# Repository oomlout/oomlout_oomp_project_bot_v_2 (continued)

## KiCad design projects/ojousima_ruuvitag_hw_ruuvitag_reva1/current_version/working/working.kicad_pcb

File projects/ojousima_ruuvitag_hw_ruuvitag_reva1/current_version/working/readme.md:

# ruuvitag_hw
 
## summary 
* id: ojousima_ruuvitag_hw_ruuvitag_reva1
* user: ojousima
* name: ruuvitag_hw
* board: ruuvitag_reva1
* repo: https://github.com/ojousima/ruuvitag_hw
* src_file_repo_kicad_pcb: ruuvitag_reva1/ruuvitag_reva1.kicad_pcb
* src_file_repo_kicad_pcb_link: https://github.com/ojousima/ruuvitag_hw/tree/master/ruuvitag_reva1/ruuvitag_reva1.kicad_pcb

* src_file_repo_sch: ruuvitag_reva1/ruuvitag_reva1.sch
* src_file_repo_sch_link: https://github.com/ojousima/ruuvitag_hw/tree/master/ruuvitag_reva1/ruuvitag_reva1.sch
* full details link: https://github.com/oomlout/oomlout_oomp_project_bot_v_2/tree/main/projects/ojousima_ruuvitag_hw_ruuvitag_reva1/current_version/working

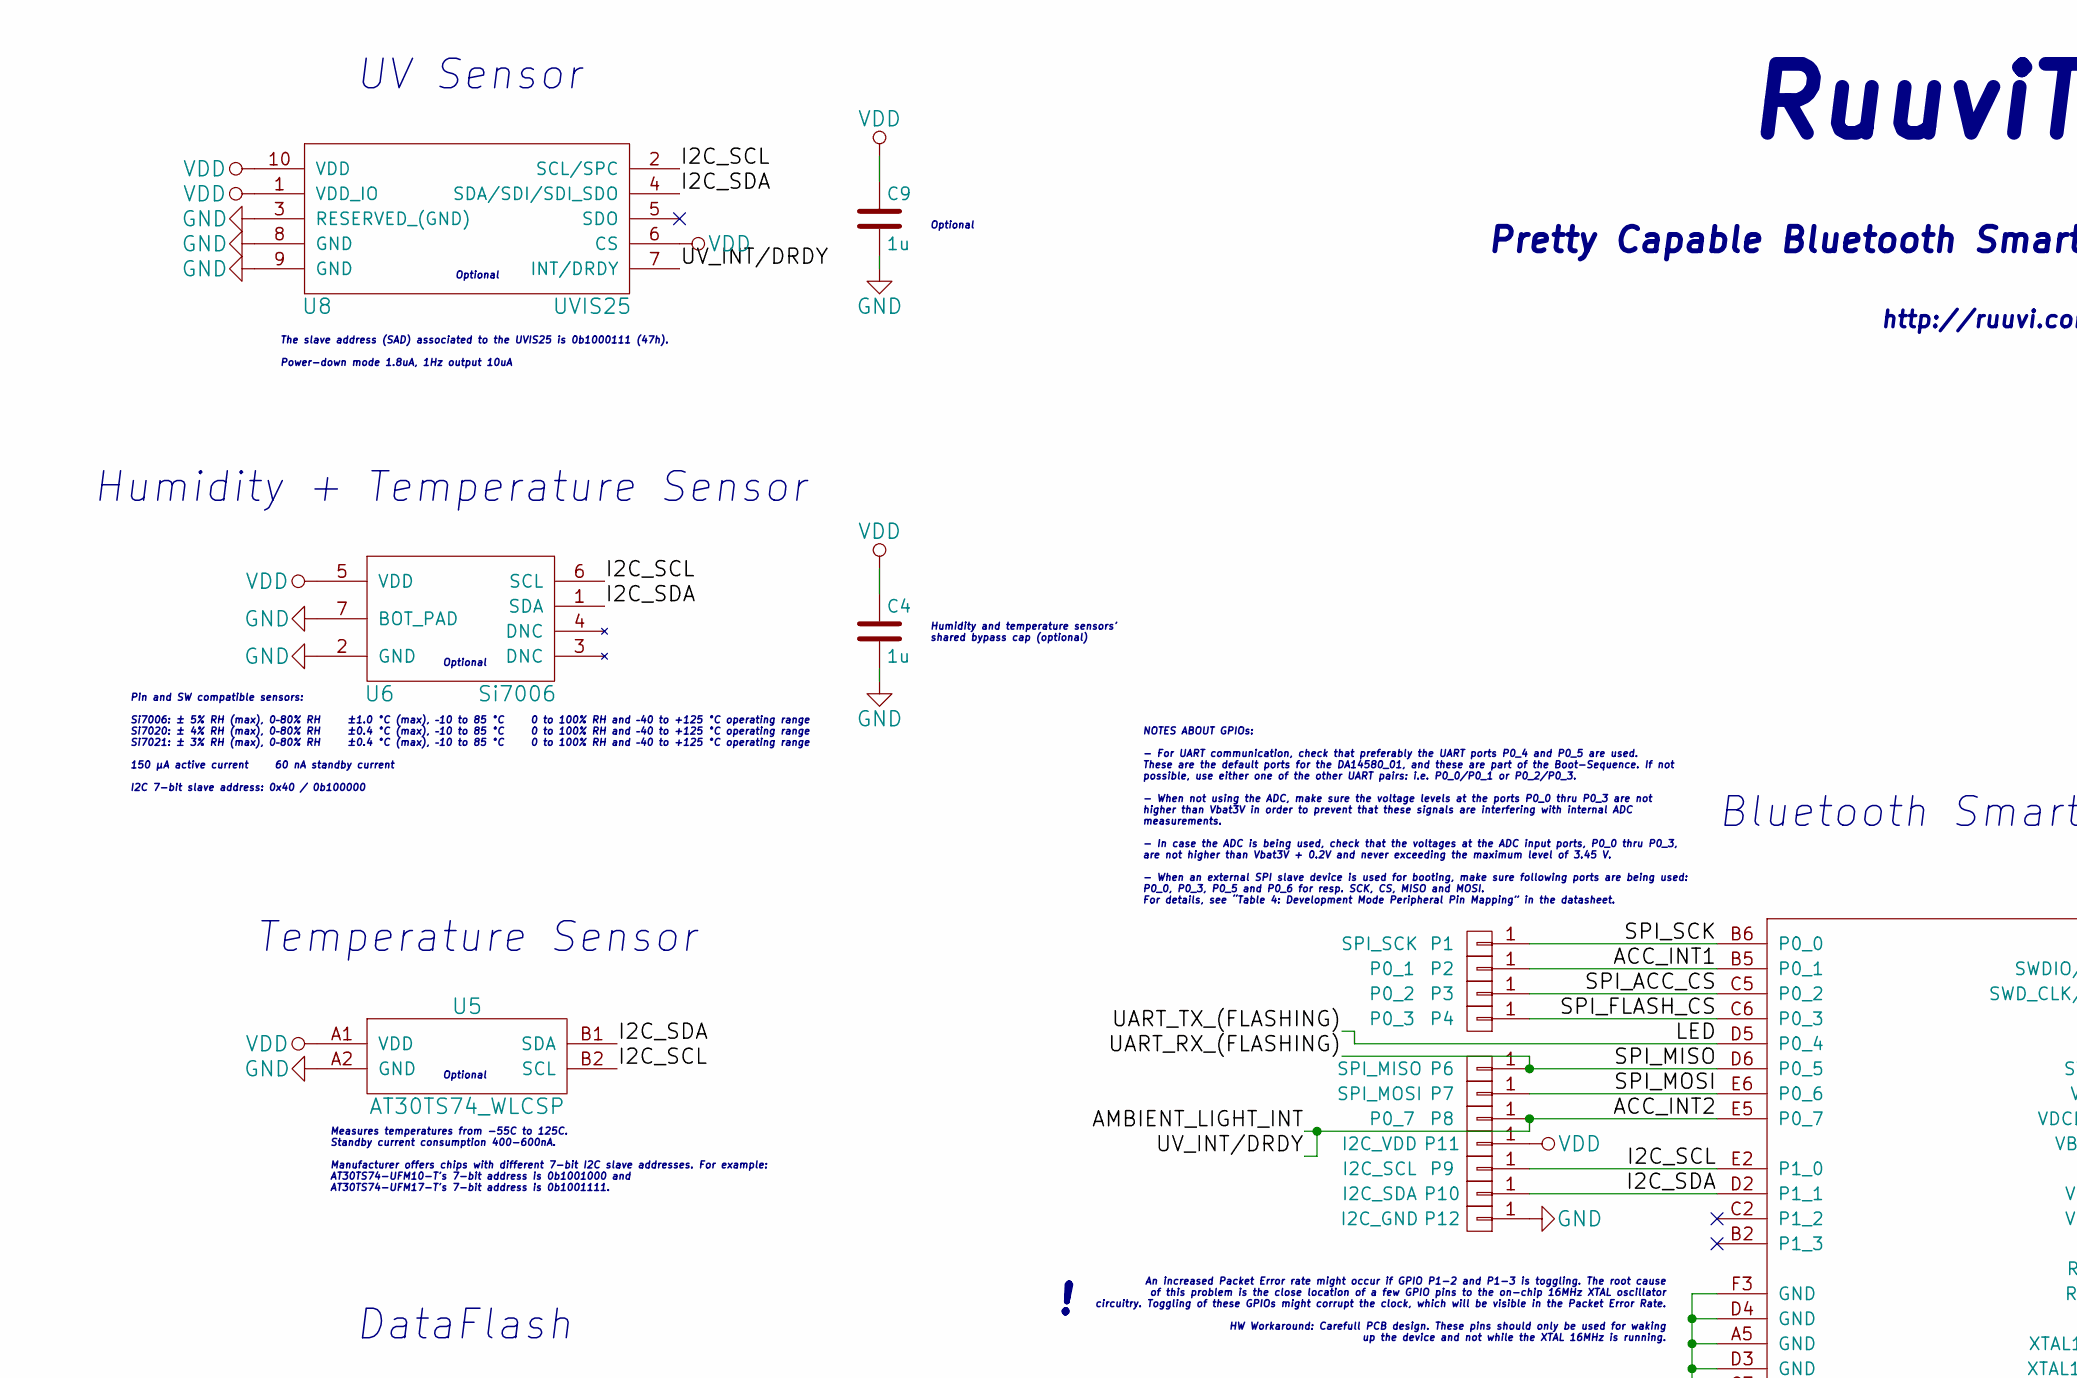
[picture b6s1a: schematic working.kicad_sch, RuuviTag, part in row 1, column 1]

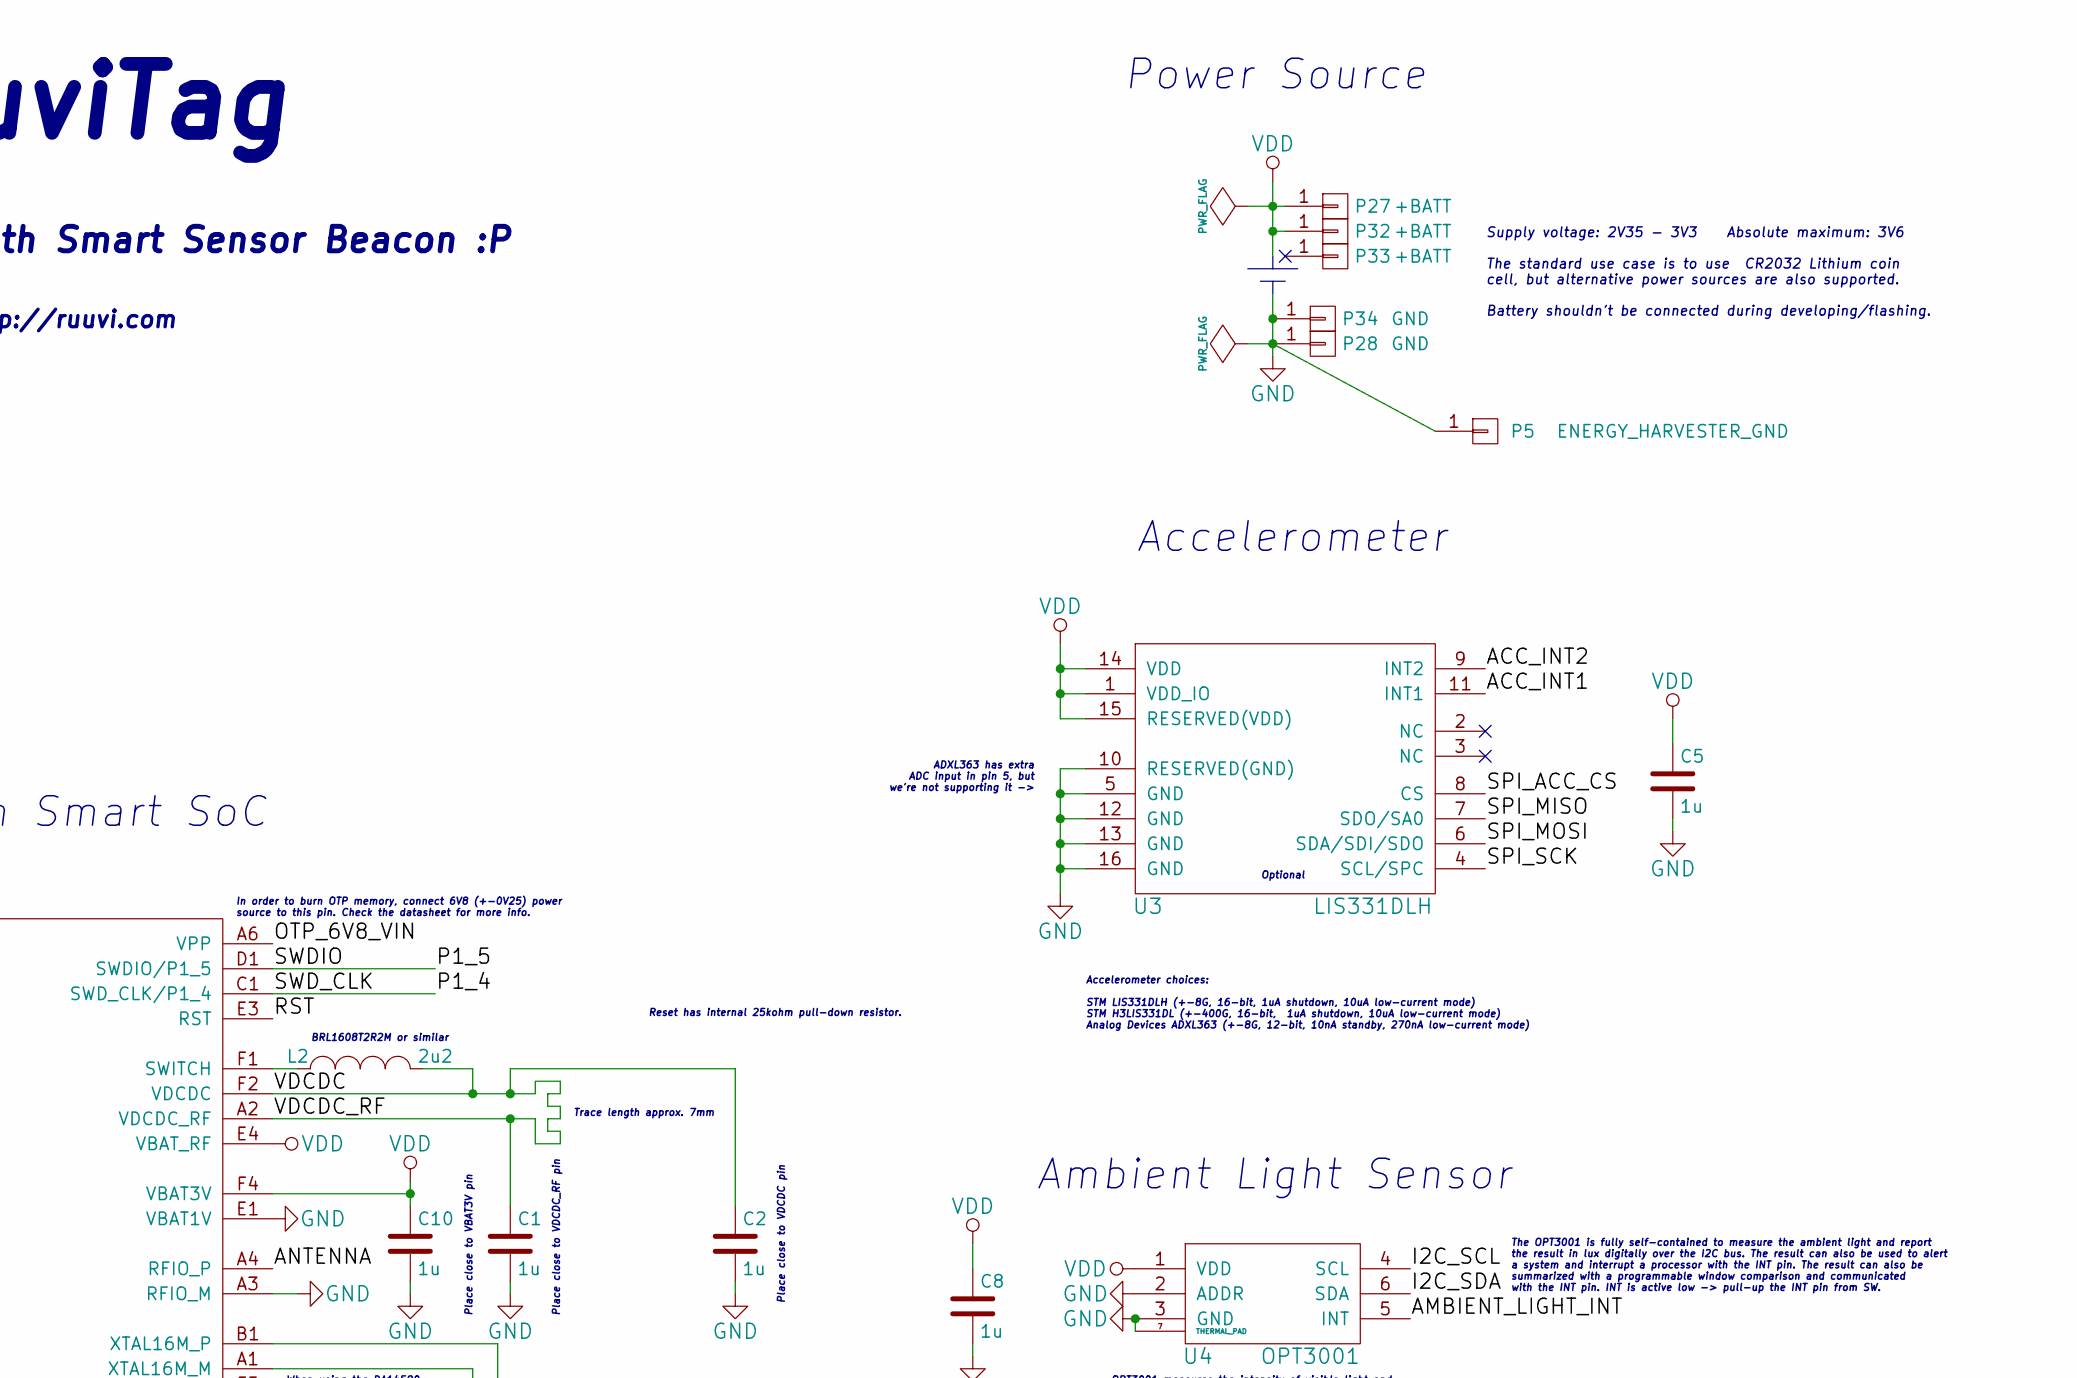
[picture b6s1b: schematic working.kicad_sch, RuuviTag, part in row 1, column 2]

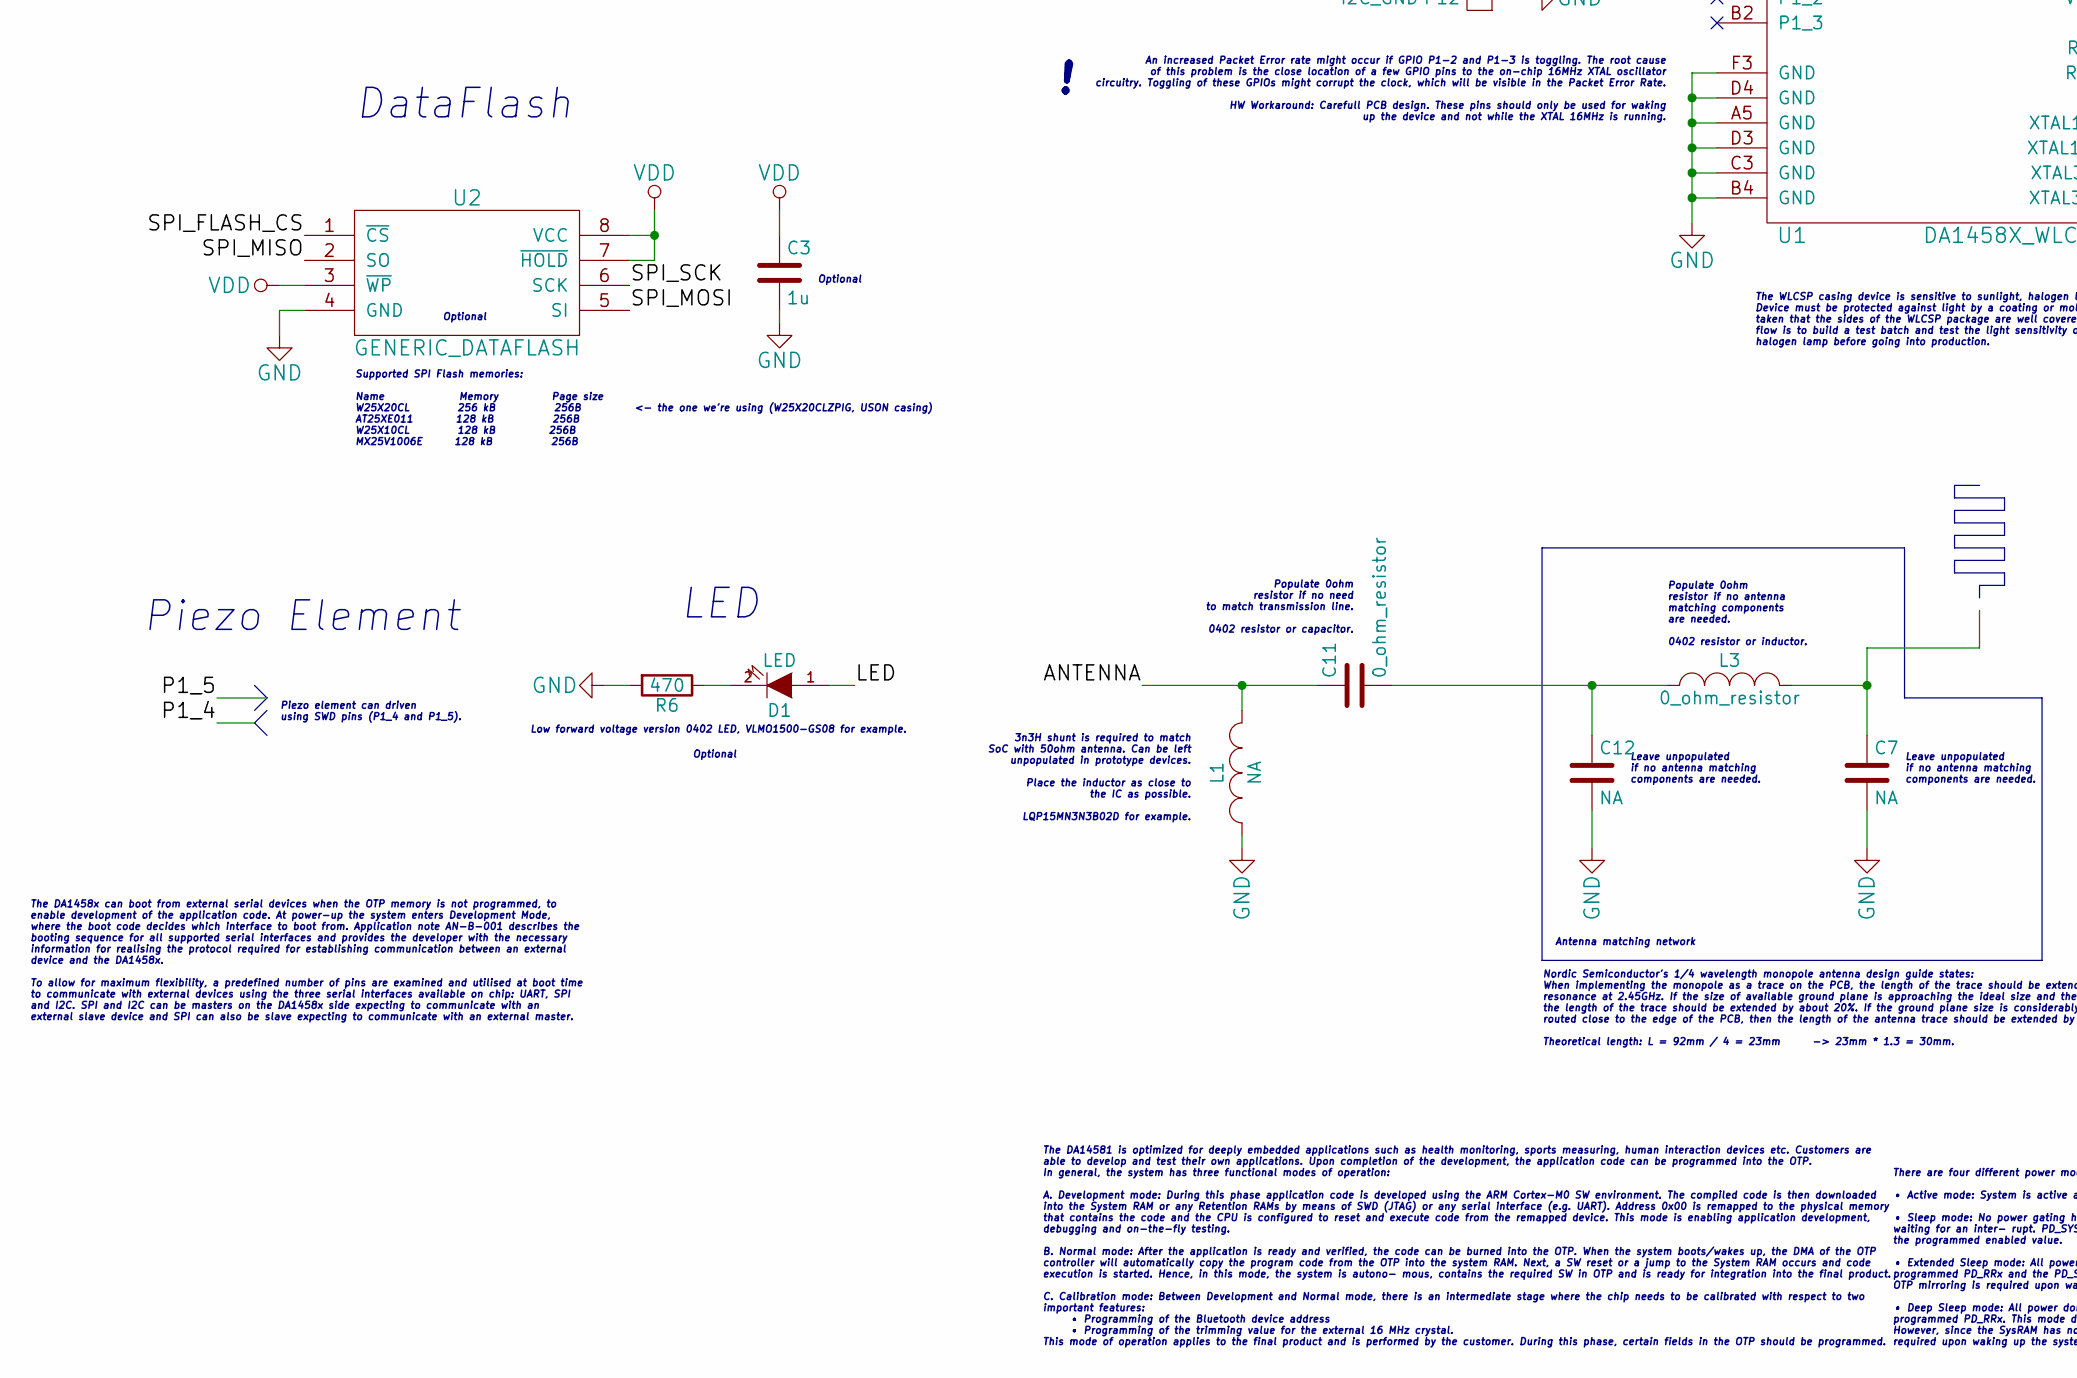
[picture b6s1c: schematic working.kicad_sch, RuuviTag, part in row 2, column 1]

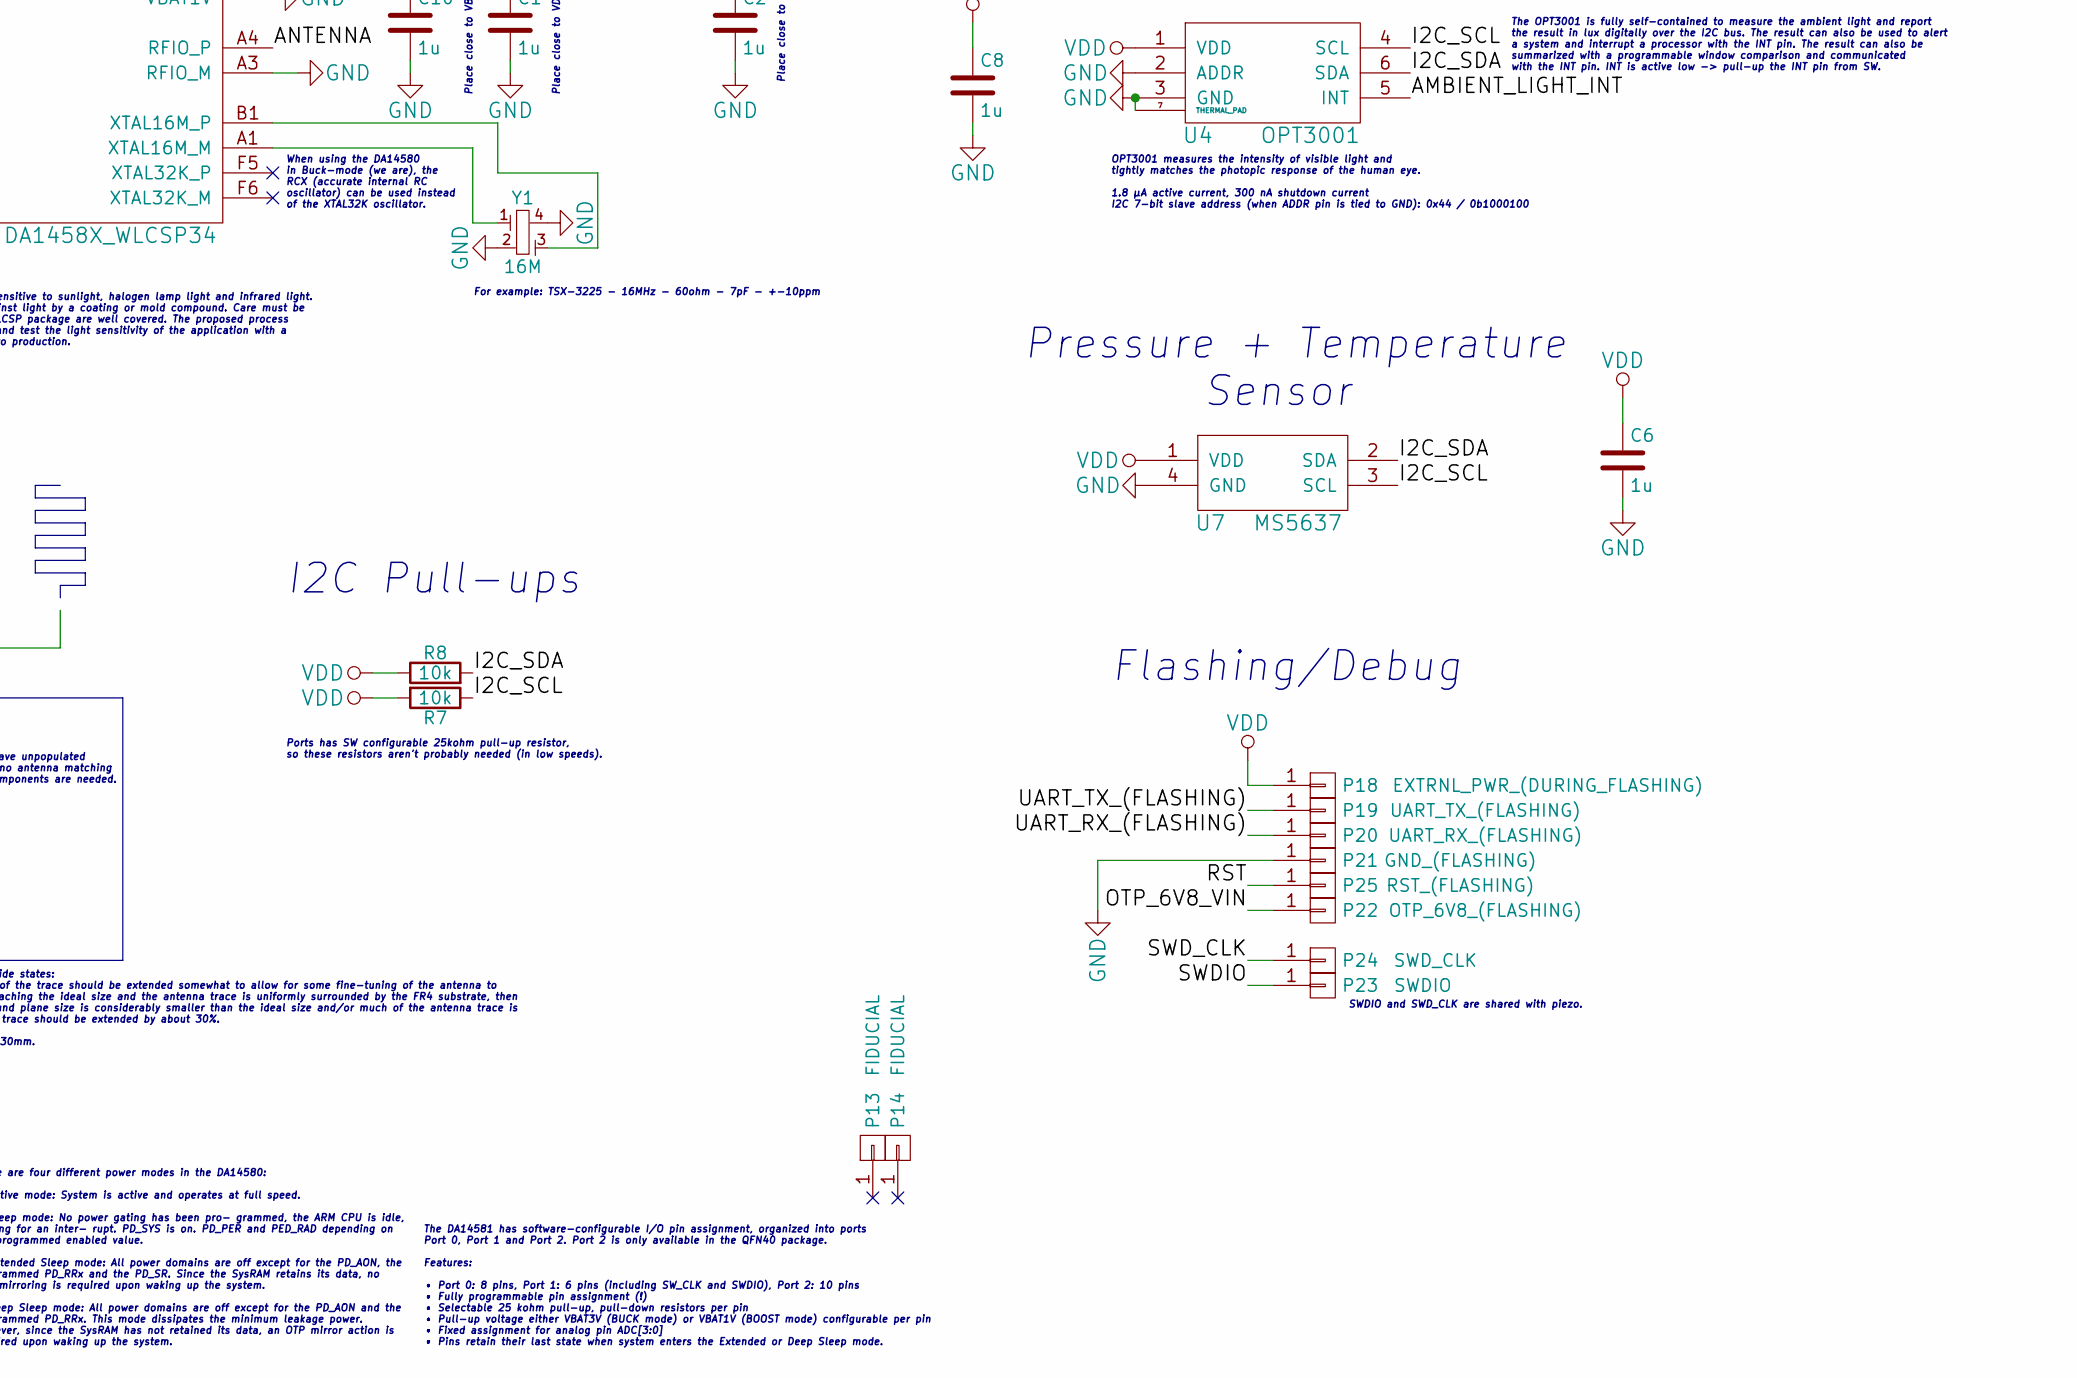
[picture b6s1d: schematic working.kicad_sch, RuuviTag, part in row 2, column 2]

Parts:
C1, C2, C3, C4, C5, C6, C8, C9, C10: 1u; 0402_GENERAL
C7, C12: NA; 0402_GENERAL
C11: 0_ohm_resistor; 0402_GENERAL
D1: LED; 0402_LED
L1: NA; 0402_GENERAL
L2: 2u2; 0603_GENERAL
L3: 0_ohm_resistor; 0402_GENERAL
P1: SPI_SCK; 05MM_PLATED_RECT_HOLE
P2: P0_1; 05MM_PLATED_RECT_HOLE
P3: P0_2; 05MM_PLATED_RECT_HOLE
P4: P0_3; 05MM_PLATED_RECT_HOLE
P5: ENERGY_HARVESTER_GND; WIDE_PLATED_HOLE2
P6: SPI_MISO; 05MM_PLATED_RECT_HOLE
P7: SPI_MOSI; 05MM_PLATED_RECT_HOLE
P8: P0_7; 05MM_PLATED_RECT_HOLE
P9: I2C_SCL; 05MM_PLATED_RECT_HOLE
P10: I2C_SDA; 05MM_PLATED_RECT_HOLE
P11: I2C_VDD; 05MM_PLATED_RECT_HOLE
P12: I2C_GND; 05MM_PLATED_RECT_HOLE
P13, P14: FIDUCIAL; 09MM_PLATED_HOLE
P18: EXTRNL_PWR_(DURING_FLASHING); 09MM_PLATED_HOLE
P19: UART_TX_(FLASHING); 09MM_PLATED_HOLE
P20: UART_RX_(FLASHING); 09MM_PLATED_HOLE
P21: GND_(FLASHING); 09MM_PLATED_HOLE
P22: OTP_6V8_(FLASHING); 09MM_PLATED_HOLE
P23: SWDIO; 09MM_PLATED_HOLE
P24: SWD_CLK; 09MM_PLATED_HOLE
P25: RST_(FLASHING); 09MM_PLATED_HOLE
P27, P32, P33: +BATT; WIDE_PLATED_HOLE
P28, P34: GND; 09MM_PLATED_HOLE
R6: 470; 0402_GENERAL
R7, R8: 10k; 0402_GENERAL
U1: DA1458X_WLCSP34; WLCSP34
U2: GENERIC_DATAFLASH; USON8_2X3MM
U3: LIS331DLH; LGA16_3X3MM
U4: OPT3001; USON6_2X2MM_WITHTHRMLPAD
U5: AT30TS74_WLCSP; WLCSP4
U6: Si7006; DFN6_3X3MM
U7: MS5637
U8: UVIS25
Y1: 16M; 32X25MM_4PIN_CRYSTAL

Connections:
/ACC_INT1: P2.1, U1.B5 (P0_1), U3.11 (INT1)
/ACC_INT2: P8.1, U1.E5 (P0_7), U3.9 (INT2), U4.5 (INT), U8.7 (INT/DRDY)
/ANTENNA: C11.1, L1.2, U1.A4 (RFIO_P)
/I2C_SCL: P9.1, R7.1, U1.E2 (P1_0), U4.4 (SCL), U5.B2 (SCL), U6.6 (SCL), U7.3 (SCL), U8.2 (SCL/SPC)
/I2C_SDA: P10.1, R8.2, U1.D2 (P1_1), U4.6 (SDA), U5.B1 (SDA), U6.1 (SDA), U7.2 (SDA), U8.4 (SDA/SDI/SDI_SDO)
/LED: D1.1 (A), P19.1, U1.D5 (P0_4)
/OTP_6V8_VIN: P22.1, U1.A6 (VPP)
/P1_4: P24.1, U1.C1 (SWD_CLK/P1_4)
/P1_5: P23.1, U1.D1 (SWDIO/P1_5)
/RST: P25.1, U1.E3 (RST)
/SPI_ACC_CS: P3.1, U1.C5 (P0_2), U3.8 (CS)
/SPI_FLASH_CS: P4.1, U1.C6 (P0_3), U2.1 (~CS)
/SPI_MISO: P6.1, P20.1, U1.D6 (P0_5), U2.2 (SO), U3.7 (SDO/SA0)
/SPI_MOSI: P7.1, U1.E6 (P0_6), U2.5 (SI), U3.6 (SDA/SDI/SDO)
/SPI_SCK: P1.1, U1.B6 (P0_0), U2.6 (SCK), U3.4 (SCL/SPC)
/VDCDC: C1.1, C2.1, L2.2, U1.A2 (VDCDC_RF), U1.F2 (VDCDC)
GND: C1.2, C2.2, C3.2, C4.2, C5.2, C6.2, C7.2, C8.2, C9.2, C10.2, C12.2, L1.1, P5.1, P12.1, P21.1, P28.1, P34.1, R6.2, U1.A3 (RFIO_M), U1.A5 (GND), U1.B4 (GND), U1.C3 (GND), U1.D3 (GND), U1.D4 (GND), U1.E1 (VBAT1V), U1.F3 (GND), U2.4 (GND), U3.5 (GND), U3.10 (RESERVED(GND)), U3.12 (GND), U3.13 (GND), U3.16 (GND), U4.2 (ADDR), U4.3 (GND), U4.7 (THERMAL_PAD), U5.A2 (GND), U6.2 (GND), U6.7 (BOT_PAD), U7.4 (GND), U8.3 (RESERVED_(GND)), U8.8 (GND), U8.9 (GND), Y1.2, Y1.4
unnamed: C7.1, L3.2
unnamed: C11.2, C12.1, L3.1
unnamed: D1.2 (K), R6.1
unnamed: L2.1, U1.F1 (SWITCH)
unnamed: U1.A1 (XTAL16M_M), Y1.1
unnamed: U1.B1 (XTAL16M_P), Y1.3
VDD: C3.1, C4.1, C5.1, C6.1, C8.1, C9.1, C10.1, P11.1, P18.1, P27.1, P32.1, R7.2, R8.1, U1.E4 (VBAT_RF), U1.F4 (VBAT3V), U2.3 (~WP), U2.7 (~HOLD), U2.8 (VCC), U3.1 (VDD_IO), U3.14 (VDD), U3.15 (RESERVED(VDD)), U4.1 (VDD), U5.A1 (VDD), U6.5 (VDD), U7.1 (VDD), U8.1 (VDD_IO), U8.6 (CS), U8.10 (VDD)

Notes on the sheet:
The OPT3001 is fully self-contained to measure the ambient light and report the result in lux digitally over the I2C bus. The result can also be used to alert a system and interrupt a processor with the INT pin. The result can also be summarized with a programmable window comparison and communicate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
Piezo Element
Optional
Power Source
Accelerometer choices: STM LIS331DLH (+-8G, 16-bit, 1uA shutdown, 10uA low-current mode) STM H3LIS331DL (+-400G, 16-bit, 1uA shutdown, 10uA low-current mode) Analog Devices ADXL363 (+-8G, 12-bit, 10nA standby, 270nA low-current mode)
The slave address (SAD) associated to the UVIS25 is 0b1000111 (47h). Power-down mode 1.8uA, 1Hz output 10uA
SWDIO and SWD_CLK are shared with piezo.
Place close to VDCDC pin
Leave unpopulated if no antenna matching components are needed.
NOTES ABOUT GPIOs: - For UART communication, check that preferably the UART ports P0_4 and P0_5 are used. These are the default ports for the DA14580_01, and these are part of the Boot-Sequence. If not possible, use either one of the other UART pairs: i.e. P0_0/P0_1 or P0_2/P0_3. - When not using t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
Accelerometer
http://ruuvi.com
Measures temperatures from -55C to 125C. Standby current consumption 400-600nA. Manufacturer offers chips with different 7-bit I2C slave addresses. For example: AT30TS74-UFM10-T's 7-bit address is 0b1001000 and AT30TS74-UFM17-T's 7-bit address is 0b1001111.
I2C Pull-ups
Ports has SW configurable 25kohm pull-up resistor, so these resistors aren't probably needed (in low speeds).
Reset has internal 25kohm pull-down resistor.
In order to burn OTP memory, connect 6V8 (+-0V25) power source to this pin. Check the datasheet for more info.
Ambient Light Sensor
BRL1608T2R2M or similar
The DA14581 is optimized for deeply embedded applications such as health monitoring, sports measuring, human interaction devices etc. Customers are able to develop and test their own applications. Upon completion of the development, the application code can be programmed into the OTP. In general, t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
For example: TSX-3225 - 16MHz - 60ohm - 7pF - +-10ppm
UV Sensor
There are four different power modes in the DA14580: • Active mode: System is active and operates at full speed. • Sleep mode: No power gating has been pro- grammed, the ARM CPU is idle, waiting for an inter- rupt. PD_SYS is on. PD_PER and PED_RAD depending on the programmed enabled value. • Extend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
When using the DA14580 in Buck-mode (we are), the RCX (accurate internal RC oscillator) can be used instead of the XTAL32K oscillator.
Populate 0ohm resistor if no need to match transmission line. 0402 resistor or capacitor.
RuuviTag
Flashing/Debug
Pretty Capable Bluetooth Smart Sensor Beacon :P
Supply voltage: 2V35 - 3V3 Absolute maximum: 3V6 The standard use case is to use CR2032 Lithium coin cell, but alternative power sources are also supported. Battery shouldn't be connected during developing/flashing.
Humidity and temperature sensors' shared bypass cap (optional)
Temperature Sensor
Pressure + Temperature Sensor
Nordic Semiconductor's 1/4 wavelength monopole antenna design guide states: When implementing the monopole as a trace on the PCB, the length of the trace should be extended somewhat to allow for some fine-tuning of the antenna to resonance at 2.45GHz. If the size of available ground plane is approa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
Low forward voltage version 0402 LED, VLMO1500-GS08 for example.
Humidity + Temperature Sensor
Trace length approx. 7mm
Piezo element can driven using SWD pins (P1_4 and P1_5).
Antenna matching network
3n3H shunt is required to match SoC with 50ohm antenna. Can be left unpopulated in prototype devices. Place the inductor as close to the IC as possible. LQP15MN3N3B02D for example.
The WLCSP casing device is sensitive to sunlight, halogen lamp light and infrared light. Device must be protected against light by a coating or mold compound. Care must be taken that the sides of the WLCSP package are well covered. The proposed process flow is to build a test batch and test the lig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

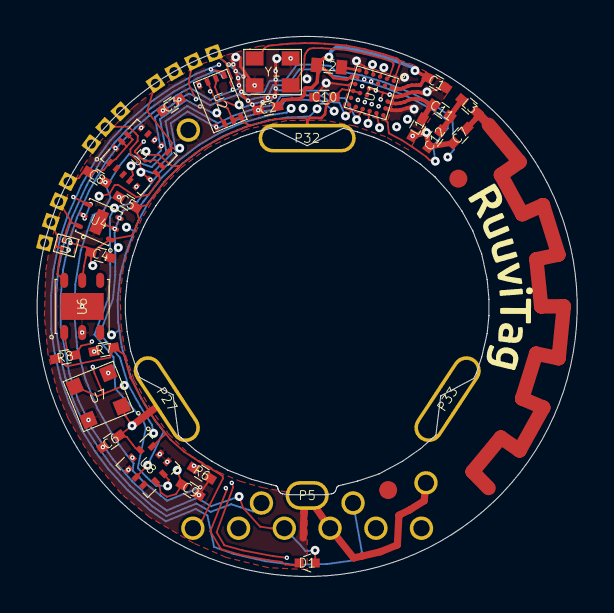
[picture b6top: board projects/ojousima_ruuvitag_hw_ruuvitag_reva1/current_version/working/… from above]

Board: 4 copper layers, 30.0 x 30.0 mm, 55 parts (0 on the bottom side), 24 nets.
